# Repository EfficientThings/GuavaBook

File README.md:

# GuavaBook
A Big(CM4)-Little(emacsOS) based laptop

VERY work in progress...

Think chromebook(but not necesarily running ChromeOS), but with a mechanical keyboard(kailh choco), 4k display, intearnal SSD and rtlSDR, and fully open source. Desighned to run an ultralight emacsOS for low power mode or just because. Fanless cooling of CM4 allows for completely silent operation and complete lack of adhesives makes the device fully repairable!

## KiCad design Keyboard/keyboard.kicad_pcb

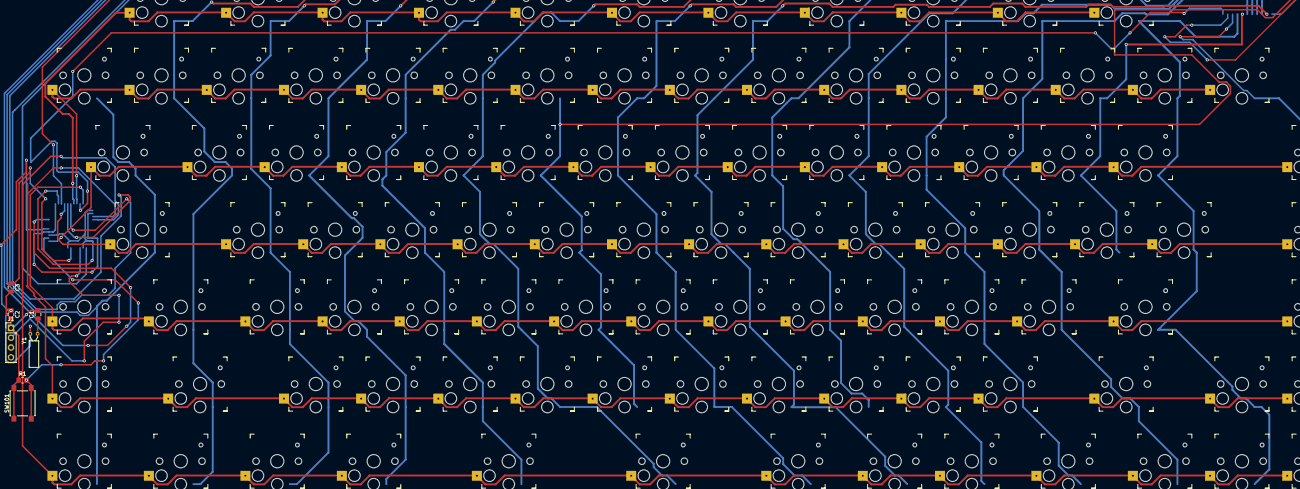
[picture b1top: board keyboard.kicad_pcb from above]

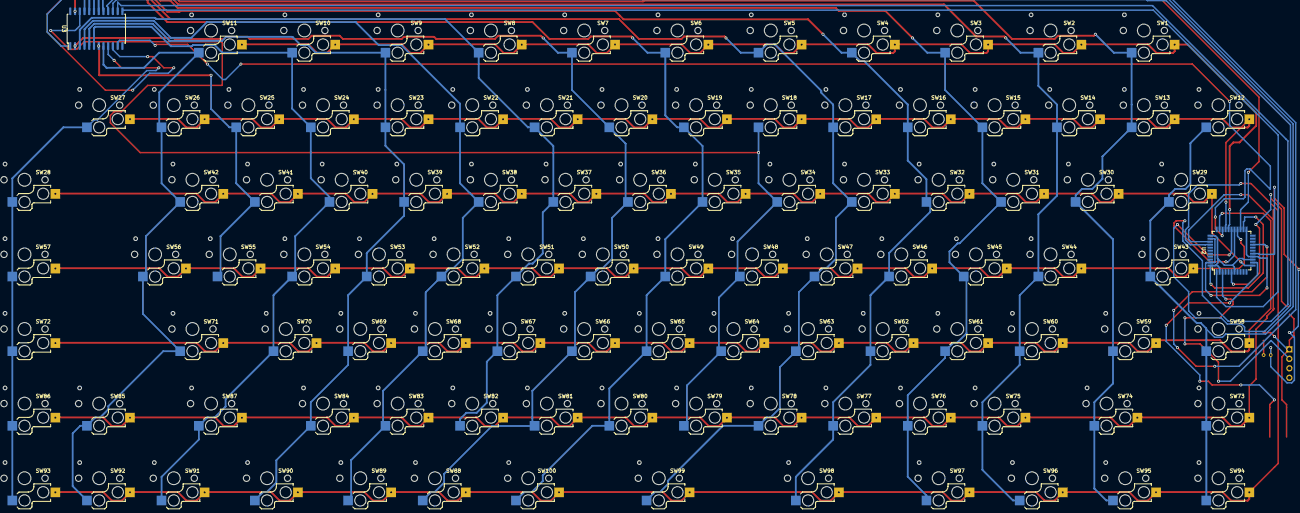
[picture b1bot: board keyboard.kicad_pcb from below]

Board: 2 copper layers, 109 parts (2 on the bottom side), 37 nets.

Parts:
C1, C2: 22pF; C_0805_2012Metric_Pad1.18x1.45mm_HandSolder
C3: 1uF; C_0805_2012Metric_Pad1.18x1.45mm_HandSolder
J1: Conn_01x04; PinHeader_1x04_P2.54mm_Vertical
R1: R_Small_US; R_0805_2012Metric_Pad1.20x1.40mm_HandSolder
SW1, SW2, SW3, SW4, SW5, SW6, SW7, SW8, SW9, SW10, SW11, SW12, SW13, SW14, SW15, SW16, SW17, SW18, SW19, SW20, SW21, SW22, SW23, SW24, SW25, SW26, SW27, SW28, SW29, SW30, SW31, SW32, SW33, SW34, SW35, SW36, SW37, SW38, SW39, SW40, SW41, SW42, SW43, SW44, SW45, SW46, SW47, SW48, SW49, SW50, SW51, SW52, SW53, SW54, SW55, SW56, SW57, SW58, SW59, SW60, SW61, SW62, SW63, SW64, SW65, SW66, SW67, SW68, SW69, SW70, SW71, SW72, SW73, SW74, SW75, SW76, SW77, SW78, SW79, SW80, SW81, SW82, SW83, SW84, SW85, SW86, SW87, SW88, SW89, SW90, SW91, SW92, SW93, SW94, SW95, SW96, SW97, SW98, SW99, SW100: SW_MEC_5G; Kailh_socket_PG1350
SW101: SW_Push; SW_Push_1P1T_NO_6x6mm_H9.5mm
U2: ATmega32U4-AU; TQFP-44_10x10mm_P0.8mm
U3: CD74HC4067M; SOIC-24W_7.5x15.4mm_P1.27mm
Y1: Crystal; Crystal_C26-LF_D2.1mm_L6.5mm_Horizontal

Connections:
+5V: J1.4, U2.2, U2.7, U2.14, U2.24, U2.34, U2.44, U3.24
GND: C1.2, C2.2, C3.2, J1.1, R1.1, SW101.1, U2.5, U2.15, U2.23, U2.35, U2.42, U2.43, U3.12
unnamed: C1.1, U2.17, Y1.2
unnamed: C2.1, U2.16, Y1.1
unnamed: C3.1, U2.6
unnamed: J1.2, U2.3
unnamed: J1.3, U2.4
unnamed: R1.2, SW101.2, U2.13
unnamed: SW1.1, SW13.1, SW30.1, SW59.1, SW74.1, SW95.1, U3.17
unnamed: SW1.3, SW2.3, SW3.3, SW4.3, SW5.3, SW6.3, SW7.3, SW8.3, SW9.3, SW10.3, SW11.3, U2.29
unnamed: SW10.1, SW24.1, SW40.1, SW54.1, SW70.1, SW87.1, SW91.1, U3.6
unnamed: SW11.1, SW26.1, SW42.1, SW56.1, SW71.1, SW85.1, SW92.1, U3.8
unnamed: SW12.1, SW29.1, SW43.1, SW58.1, SW73.1, SW94.1, U3.16
unnamed: SW12.3, SW13.3, SW14.3, SW15.3, SW16.3, SW17.3, SW18.3, SW19.3, SW20.3, SW21.3, SW22.3, SW23.3, SW24.3, SW25.3, SW26.3, SW27.3, U2.30
unnamed: SW2.1, SW14.1, SW44.1, SW60.1, SW75.1, SW96.1, U3.18
unnamed: SW3.1, SW15.1, SW31.1, SW45.1, SW61.1, SW76.1, SW97.1, U3.19
unnamed: SW4.1, SW16.1, SW32.1, SW46.1, SW62.1, SW77.1, SW98.1, U3.20
unnamed: SW5.1, SW17.1, SW33.1, SW47.1, SW63.1, SW78.1, SW99.1, U3.21
unnamed: SW18.1, SW34.1, SW48.1, SW64.1, SW79.1, U3.22
unnamed: SW7.1, SW20.1, SW36.1, SW50.1, SW66.1, SW81.1, SW88.1, U3.2
unnamed: SW8.1, SW21.1, SW37.1, SW51.1, SW67.1, SW82.1, U3.3
unnamed: SW22.1, SW38.1, SW52.1, SW68.1, SW83.1, SW89.1, U3.4
unnamed: SW9.1, SW23.1, SW39.1, SW53.1, SW69.1, SW84.1, SW90.1, U3.5
unnamed: SW25.1, SW41.1, SW55.1, U3.7
unnamed: SW27.1, SW28.1, SW57.1, SW72.1, SW86.1, SW93.1, U3.9
unnamed: SW28.3, SW29.3, SW30.3, SW31.3, SW32.3, SW33.3, SW34.3, SW35.3, SW36.3, SW37.3, SW38.3, SW39.3, SW40.3, SW41.3, SW42.3, U2.12
unnamed: SW43.3, SW44.3, SW45.3, SW46.3, SW47.3, SW48.3, SW49.3, SW50.3, SW51.3, SW52.3, SW53.3, SW54.3, SW55.3, SW56.3, SW57.3, U2.26
unnamed: SW58.3, SW59.3, SW60.3, SW61.3, SW62.3, SW63.3, SW64.3, SW65.3, SW66.3, SW67.3, SW68.3, SW69.3, SW70.3, SW71.3, SW72.3, U2.32
unnamed: SW73.3, SW74.3, SW75.3, SW76.3, SW77.3, SW78.3, SW79.3, SW80.3, SW81.3, SW82.3, SW83.3, SW84.3, SW85.3, SW86.3, SW87.3, U2.36
unnamed: SW6.1, SW19.1, SW35.1, SW49.1, SW65.1, SW80.1, SW100.1, U3.23
unnamed: SW88.3, SW89.3, SW90.3, SW91.3, SW92.3, SW93.3, SW94.3, SW95.3, SW96.3, SW97.3, SW98.3, SW99.3, SW100.3, U2.37
unnamed: U2.1, U3.13
unnamed: U2.19, U3.1
unnamed: U2.25, U3.10
unnamed: U2.27, U3.14
unnamed: U2.28, U3.15
unnamed: U2.31, U3.11

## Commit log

2021-02-24 Add PCB files
2021-02-25 add some parts
2021-02-25 add hierachy pins
2021-02-26 add some power stuff and an extra USB port
2021-02-26 switch out battery IC for better charging current
2021-02-26 add key matrix and assighn footprints
2021-02-26 space out keyswitches for standard caps!
2021-02-27 route keyboard
2021-02-27 move power dilevery to a hierarchy sheet and wire HDMI1
2021-02-28 Add usb 3 chip in hierarchy sheet and wire ports
2021-03-01 add pcie nets, intearnal hub and ports
2021-03-01 partial redo of keyboard, invert differential pairs on USB conn
2021-03-02 mostly replace keyboard
2021-03-02 finish keyboard, do some USB/PCIe routing
2021-03-03 remove USB ss HUB IC and add onboard USB SATA bridge
2021-03-04 split into two boards
